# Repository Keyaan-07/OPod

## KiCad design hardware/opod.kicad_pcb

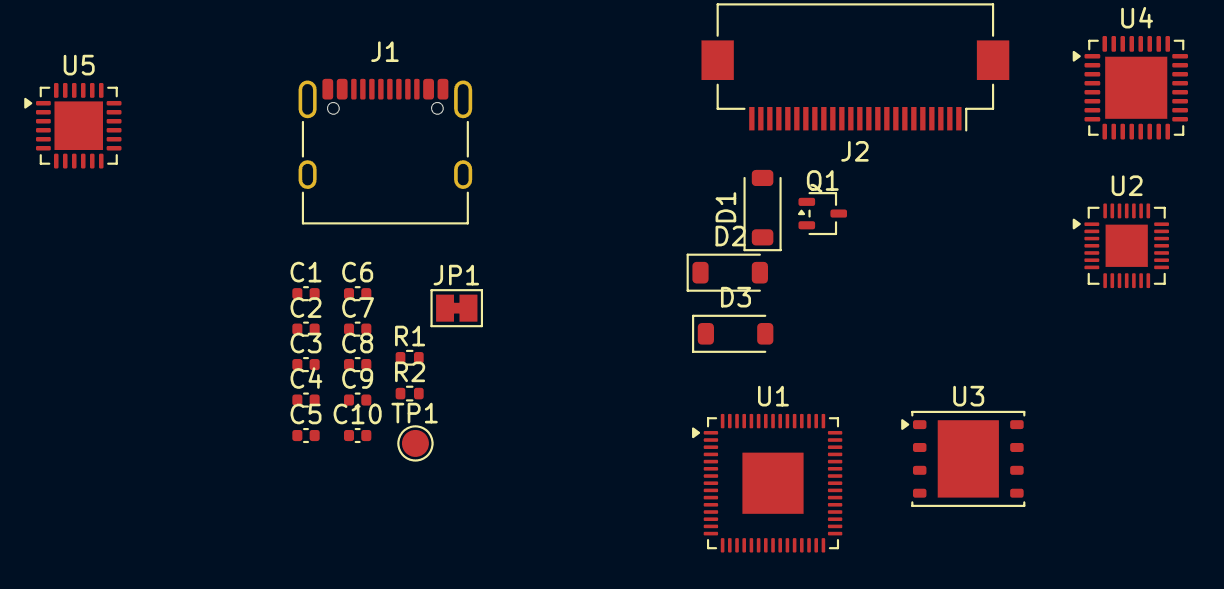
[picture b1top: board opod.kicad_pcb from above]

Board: 2 copper layers, 25 parts (0 on the bottom side), 23 nets, no tracks yet.

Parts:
C1, C3: 4.7u; C_0402_1005Metric
C2, C4, C5, C6, C7, C8, C9, C10: 1u; C_0402_1005Metric
D1, D2, D3: MBR0530; D_SOD-123
J1: USB_C_Receptacle_USB2.0_16P; USB_C_Receptacle_XKB_U262-16XN-4BVC11
J2: Conn_01x24_Pin; Hirose_FH12-24S-0.5SH_1x24-1MP_P0.50mm_Horizontal
JP1: Jumper_2_Bridged; SolderJumper-2_P1.3mm_Bridged_Pad1.0x1.5mm
Q1: Si1308EDL; SOT-323_SC-70
R1: 2.2; R_0402_1005Metric
R2: 1M; R_0402_1005Metric
TP1: TestPoint; TestPoint_Pad_D1.5mm
U1: RP2350A; QFN-60-1EP_7x7mm_P0.4mm_EP3.4x3.4mm
U2: MTCH6102; UQFN-28-1EP_4x4mm_P0.4mm_EP2.35x2.35mm
U3: W25Q128JVP; WSON-8-1EP_6x5mm_P1.27mm_EP3.4x4.3mm
U4: TLV320DAC3101; QFN-32-1EP_5x5mm_P0.5mm_EP3.45x3.45mm
U5: BQ25895RTW; Texas_RTW_WQFN-24-1EP_4x4mm_P0.5mm_EP2.7x2.7mm

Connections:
+3V3: C3.1, C5.2, J2.15, J2.16
/display/BS1: J2.8, JP1.2 (B), TP1.1 (1_1)
/display/GDR: J2.2, Q1.1 (G), R2.1
/display/RESE: J2.3, Q1.2 (S), R1.1
/display/VCOM: C8.2, J2.24
/display/VDD: C6.2, J2.18
/display/VGH: C2.1, D3.1 (K), J2.21
/display/VGL: C7.2, D1.2 (A), J2.23
/display/VSH1: C10.2, J2.20
/display/VSH2: C4.2, J2.5
/display/VSL: C9.2, J2.22
GND: C2.2, C3.2, C4.1, C5.1, C6.1, C7.1, C8.1, C9.1, C10.1, D2.1 (K), J1.A1 (GND), J1.A12 (GND), J1.B1 (GND), J1.B12 (GND), J2.17, JP1.1 (A), R1.2, R2.2
MAIN_DN: J1.A7 (D-), J1.B7 (D-)
MAIN_DP: J1.A6 (D+), J1.B6 (D+)
unnamed: C1.1, D1.1 (K), D2.2 (A)
unnamed: C1.2, D3.2 (A), Q1.3 (D)
unnamed: U1.6 (DVDD), U1.23 (DVDD), U1.39 (DVDD)
unnamed: U1.1 (IOVDD), U1.11 (IOVDD), U1.20 (IOVDD), U1.30 (IOVDD), U1.38 (IOVDD), U1.45 (IOVDD)
unnamed: U5.13 (BAT), U5.14 (BAT)
unnamed: U5.17 (PGND), U5.18 (PGND), U5.25 (PGND)
unnamed: U5.19 (SW), U5.20 (SW)
unnamed: U5.15 (SYS), U5.16 (SYS)
VBUS: J1.A4 (VBUS), J1.A9 (VBUS), J1.B4 (VBUS), J1.B9 (VBUS), U5.1 (VBUS)

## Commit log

2026-06-04 Hello, World!
2026-06-05 Hello, World x2
2026-06-06 wiring stuff
2026-06-07 charging circuit
